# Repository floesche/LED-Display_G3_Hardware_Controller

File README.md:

---
title: Controller PCB
parent: Generation 3
---

# panels_controller_design  

CAD design files, gerber files and parts list for the Panels Controller.

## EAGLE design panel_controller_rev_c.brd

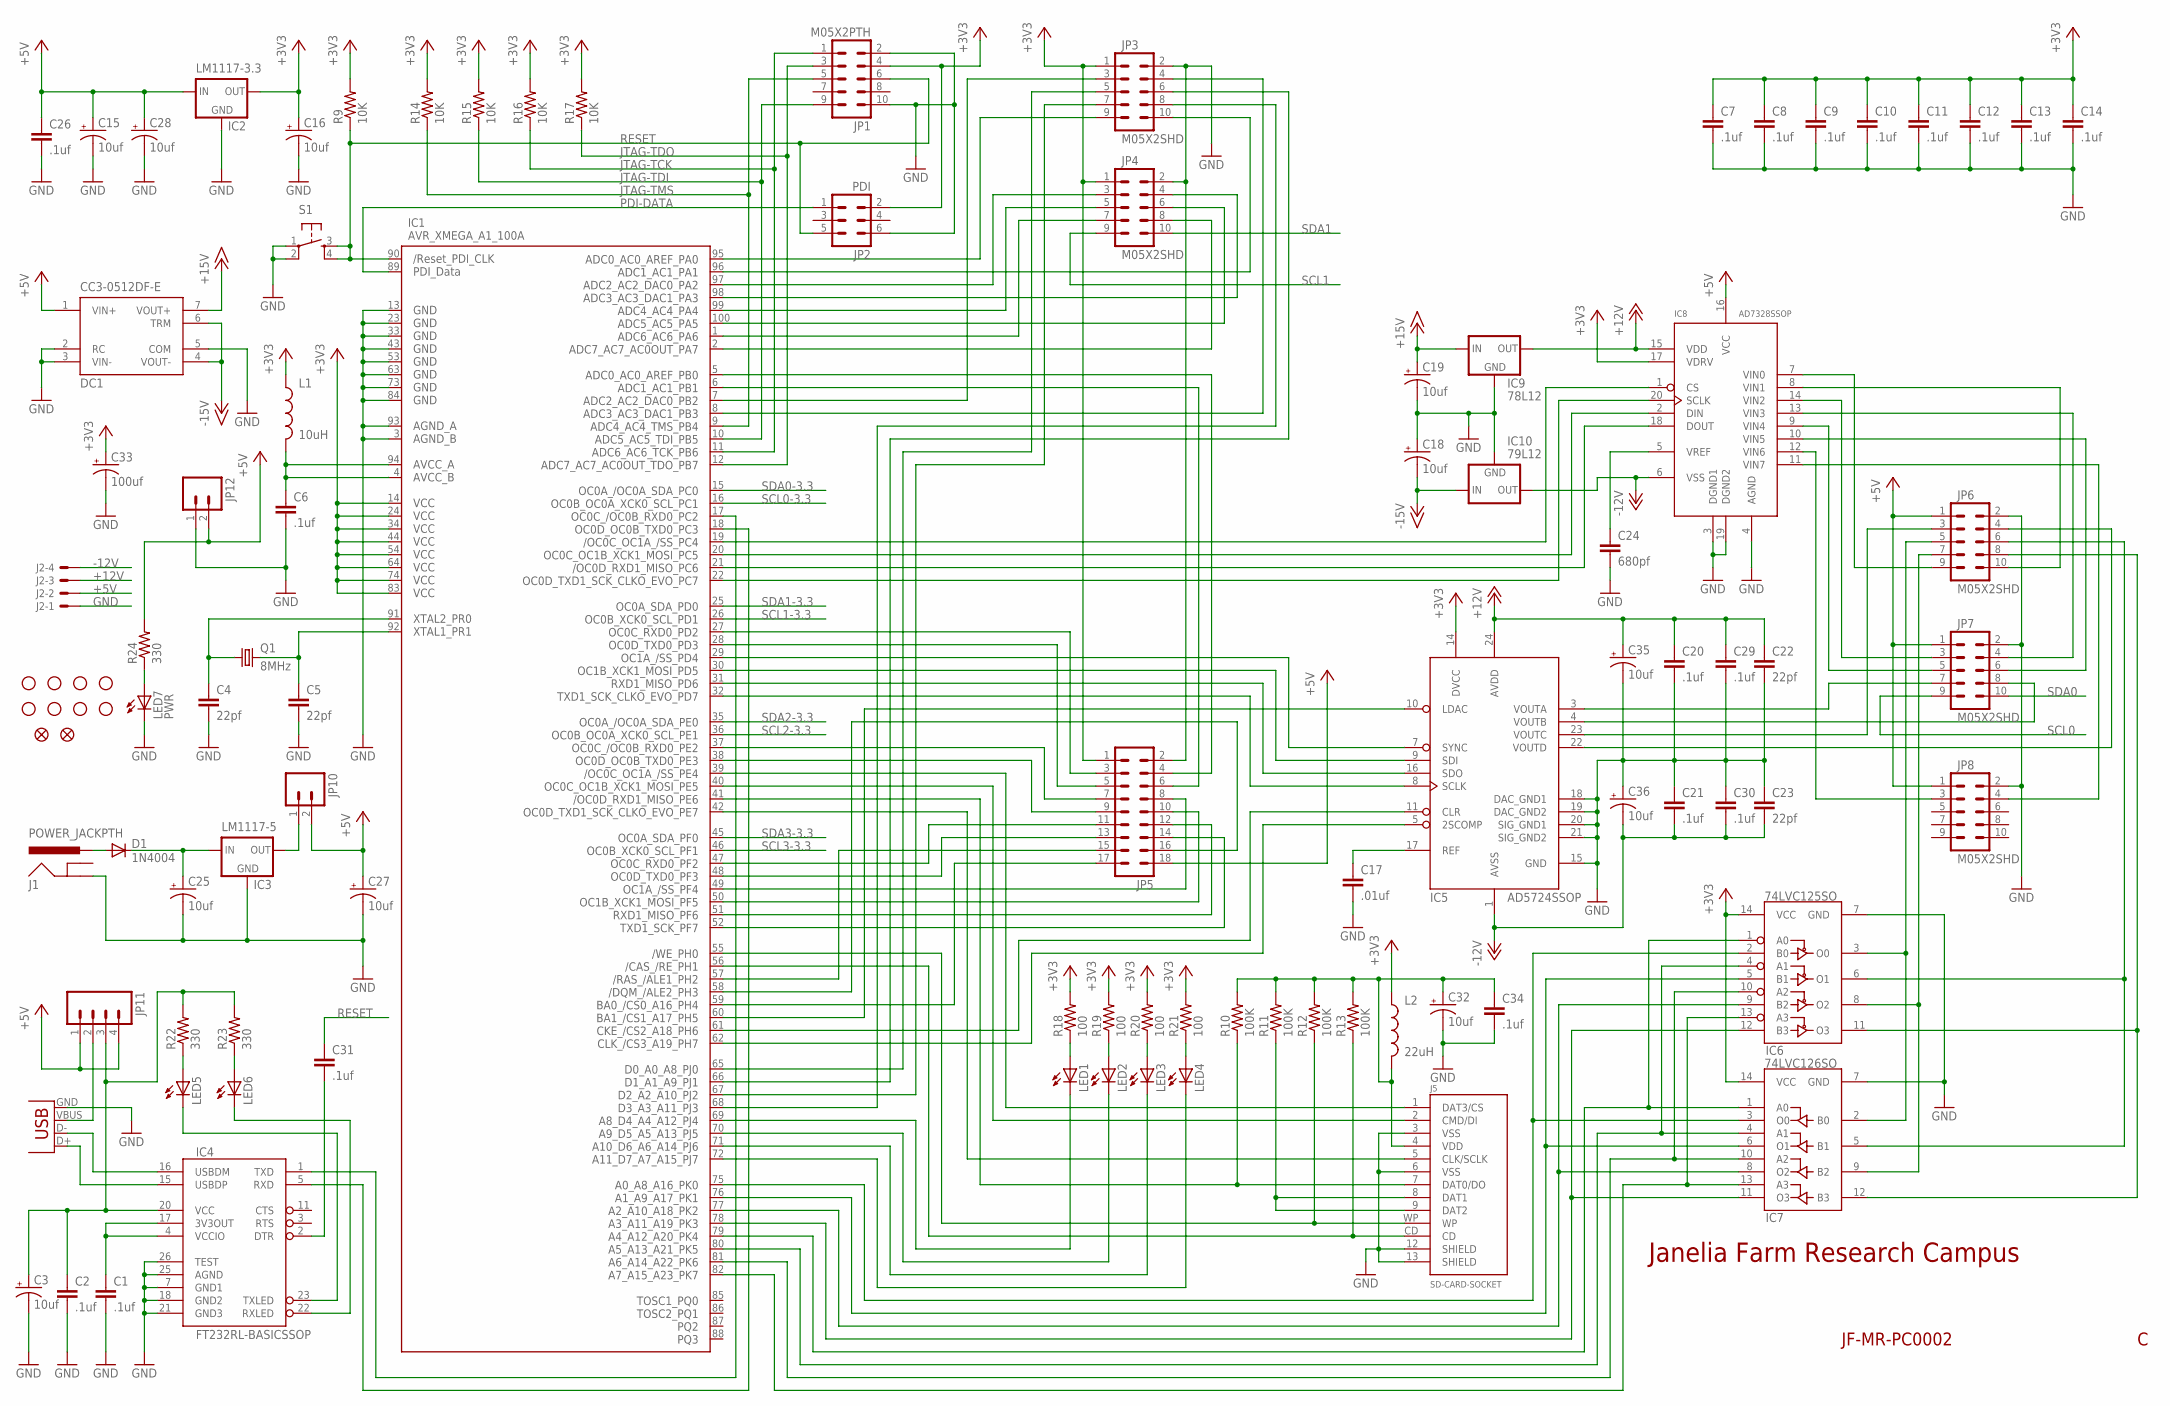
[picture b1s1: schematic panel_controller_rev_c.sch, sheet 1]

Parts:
C1, C2, C6, C7, C8, C9, C10, C11, C12, C13, C14, C20, C21, C26, C29, C30, C31, C34: .1uf; 0603
C3, C15, C16, C18, C19, C25, C27, C28, C32, C35, C36: 10uf; EIA3216
C4, C5, C22, C23: 22pf; 0603
C17: .01uf; 0603
C24: 680pf; 0603
C33: 100uf; PANASONIC_E
D1: 1N4004; DO41-10
DC1: CC3-0512DF-E; CC3-TH
IC1: AVR_XMEGA_A1_100A; TQFP100
IC2: LM1117-3.3; SOT223
IC3: LM1117-5; SOT223
IC4: FT232RL-BASICSSOP; SSOP28DB
IC5: AD5724SSOP; TSSOP24
IC6: 74LVC125SO; SO014
IC7: 74LVC126SO; SO014
IC8: AD7328SSOP; TSSOP20
IC9: 78L12; SOT89
IC10: 79L12; SOT89
J1: POWER_JACKPTH; POWER_JACK_PTH
J2: KK-156-4
J3: USBPTH; USB-B-PTH
J5: SD-CARD-SOCKET; SD-MMC_SOCKET-3M
JP1: M05X2PTH; MA05-2
JP2: PDI; MA03-2
JP3, JP4, JP6, JP7, JP8: M05X2SHD; 2X5-SHROUDED
JP5: MA09-2
JP10, JP12: M02PTH; 1X02
JP11: M04PTH; 1X04
L1: 10uH; 0805
L2: 22uH; 0805
LED1, LED2, LED3, LED4, LED5, LED6: LED3MM
LED7: PWR; LED3MM
Q1: 8MHz; HC49UP
R9, R14, R15, R16, R17: 10K; 0603
R10, R11, R12, R13: 100K; 0603
R18, R19, R20, R21: 100; 0603
R22, R23, R24: 330; 0603
S1: TAC_SWITCHB3S-1000; OMRON
U$1, U$2: FIDUCIAL1X2; FIDUCIAL-1X2
U$3, U$4, U$5, U$6, U$7, U$8, U$9, U$10: STAND-OFF

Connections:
+3V3: C7.1, C8.1, C9.1, C10.1, C11.1, C12.1, C13.1, C14.1, C16.A (+), C33.+, IC1.14 (VCC1), IC1.24 (VCC2), IC1.34 (VCC3), IC1.44 (VCC4), IC1.54 (VCC5), IC1.64 (VCC6), IC1.74 (VCC7), IC1.83 (VCC8), IC2.2 (OUT), IC5.14 (DVCC), IC6.14 (VCC), IC7.14 (VCC), IC8.17 (VDRV), JP1.4, JP2.2, JP3.1, JP4.1, JP5.1, L1.1, L2.1, R9.2, R14.2, R15.2, R16.2, R17.2, R18.2, R19.2, R20.2, R21.2; also elsewhere on the board
+5V: C15.A (+), C26.1, C27.A (+), C28.A (+), DC1.1 (VIN+), IC2.3 (IN), IC8.16 (VCC), J2.2, JP5.18, JP6.1, JP7.1, JP8.1, JP10.2, JP11.1, JP11.4, JP12.2, R24.2; also elsewhere on the board
+12V: C20.1, C22.1, C29.1, C35.A (+), IC5.24 (AVDD), IC8.15 (VDD), IC9.1 (OUT), J2.3
+15V: C19.A (+), DC1.7 (VOUT+), IC9.3 (IN)
-12V: C21.2, C23.2, C30.2, C36.C (-), IC5.1 (AVSS), IC8.6 (VSS), IC10.3 (OUT), J2.4
-15V: C18.C (-), DC1.4 (VOUT-), DC1.6 (TRM), IC10.2 (IN)
GND: C1.2, C2.2, C3.C (-), C4.2, C5.2, C6.2, C7.2, C8.2, C9.2, C10.2, C11.2, C12.2, C13.2, C14.2, C15.C (-), C16.C (-), C17.2, C18.A (+), C19.C (-), C20.2, C21.1, C22.2, C23.1, C24.2, C25.C (-), C26.2, C27.C (-), C28.C (-), C29.2, C30.1, C32.C (-), C33.-, C34.2, C35.C (-), C36.A (+), DC1.2 (RC), DC1.3 (VIN-), DC1.5 (COM), IC1.3 (AGND_B), IC1.13 (GND1), IC1.23 (GND2), IC1.33 (GND3), IC1.43 (GND4), IC1.53 (GND5), IC1.63 (GND6), IC1.73 (GND7), IC1.84 (GND8), IC1.93 (AGND_A), IC2.1 (GND), IC3.1 (GND), IC4.7 (GND1), IC4.18 (GND2), IC4.21 (GND3), IC4.25 (AGND), IC4.26 (TEST), IC5.15 (GND), IC5.18 (DAC_GND1), IC5.19 (DAC_GND2), IC5.20 (SIG_GND1), IC5.21 (SIG_GND2), IC6.7 (GND), IC7.7 (GND), IC8.3 (DGND1), IC8.4 (AGND), IC8.19 (DGND2), IC9.2 (GND), IC10.1 (GND), J1.GND, J2.1, J3.GND, J5.3 (VSS), J5.6 (VSS), J5.12 (SHIELD), J5.13 (SHIELD), JP1.2, JP1.10, JP2.6, JP3.2, JP4.2, JP5.2, JP6.2, JP7.2, JP8.2, JP12.1, LED7.K (C), S1.1, S1.2; also elsewhere on the board
JTAG-TCK: IC1.11 (PB6), JP1.1, R16.1
JTAG-TDI: IC1.10 (PB5), JP1.9, R15.1
JTAG-TDO: IC1.12 (PB7), JP1.3, R17.1
JTAG-TMS: IC1.9 (PB4), JP1.5, R14.1
unnamed: IC4.16 (USBDM), J3.D-
unnamed: IC4.15 (USBDP), J3.D+
unnamed: J3.VBUS, JP11.2
unnamed: C1.1, IC4.4 (VCCIO), IC4.17 (3V3OUT)
unnamed: IC1.18 (PC3), IC4.5 (RXD)
unnamed: IC1.19 (PC4), IC8.1 (CS)
unnamed: IC1.57 (PH2), JP5.15
unnamed: IC1.65 (PJ0), JP3.5
unnamed: IC1.67 (PJ2), JP3.7
unnamed: IC1.17 (PC2), IC4.1 (TXD)
unnamed: LED5.A, R22.1
unnamed: IC1.40 (PE5), J5.2 (CMD/DI)
unnamed: IC1.41 (PE6), J5.7 (DAT0/DO), R10.1
unnamed: IC1.42 (PE7), J5.5 (CLK/SCLK)
unnamed: IC1.39 (PE4), J5.1 (DAT3/CS)
unnamed: IC1.69 (PJ4), LED1.K (C)
unnamed: IC1.70 (PJ5), LED2.K (C)
unnamed: C4.1, IC1.91 (PR0), Q1.1
unnamed: C5.1, IC1.92 (PR1), Q1.2
unnamed: IC1.71 (PJ6), LED3.K (C)
unnamed: IC1.72 (PJ7), LED4.K (C)
unnamed: LED1.A, R18.1
unnamed: C6.1, IC1.4 (AVCC_B), IC1.94 (AVCC_A), L1.2
unnamed: LED2.A, R19.1
unnamed: LED3.A, R20.1
unnamed: LED4.A, R21.1
unnamed: IC1.66 (PJ1), JP3.6
unnamed: IC1.68 (PJ3), JP3.8
unnamed: IC1.2 (PA7), JP4.8
unnamed: IC1.1 (PA6), JP4.7
unnamed: IC1.100 (PA5), JP4.6
unnamed: J5.8 (DAT1), J5.9 (DAT2), R11.1
unnamed: IC1.55 (PH0), J5.WP, R12.1
unnamed: IC1.56 (PH1), J5.CD, R13.1
unnamed: IC1.99 (PA4), JP4.5
unnamed: IC1.98 (PA3), JP4.4
unnamed: IC1.97 (PA2), JP4.3
unnamed: IC1.96 (PA1), JP3.10
unnamed: IC1.95 (PA0), JP3.9
unnamed: IC1.7 (PB2), JP3.3
unnamed: IC1.8 (PB3), JP3.4
unnamed: IC1.20 (PC5), IC8.2 (DIN)
unnamed: IC1.22 (PC7), IC8.20 (SCLK)
unnamed: IC1.21 (PC6), IC8.18 (DOUT)
unnamed: IC1.32 (PD7), IC5.8 (SCLK)
unnamed: LED6.A, R23.1
unnamed: C24.1, IC8.5 (VREF)
unnamed: IC1.31 (PD6), IC5.16 (SDO)
unnamed: IC1.30 (PD5), IC5.9 (SDI)
unnamed: IC1.29 (PD4), IC5.7 (SYNC)
unnamed: IC1.61 (PH6), IC5.11 (CLR)
unnamed: C17.1, IC5.17 (REF)
unnamed: IC1.37 (PE2), JP5.7
unnamed: IC1.38 (PE3), JP5.9
unnamed: IC1.27 (PD2), JP5.3
unnamed: IC1.28 (PD3), JP5.5
unnamed: IC1.5 (PB0), JP5.4
unnamed: IC1.6 (PB1), JP5.6
unnamed: IC1.47 (PF2), JP5.11
unnamed: IC1.48 (PF3), JP5.13
unnamed: IC1.49 (PF4), JP5.8
unnamed: IC1.50 (PF5), JP5.10
unnamed: IC1.51 (PF6), JP5.12
unnamed: IC1.52 (PF7), JP5.14
unnamed: IC1.62 (PH7), IC5.5 (2SCOMP)
unnamed: IC1.75 (PK0), IC6.2 (B0), IC7.3 (O0)
unnamed: IC1.76 (PK1), IC6.5 (B1), IC7.6 (O1)
unnamed: IC1.77 (PK2), IC6.9 (B2), IC7.8 (O2)
unnamed: IC1.78 (PK3), IC6.12 (B3), IC7.11 (O3)
unnamed: IC1.79 (PK4), IC6.1 (A0), IC7.1 (A0)
unnamed: C2.1, C3.A (+), IC4.20 (VCC), JP11.3, R22.2, R23.2
unnamed: IC4.22 (RXLED), LED6.K (C)
unnamed: IC1.60 (PH5), IC5.10 (LDAC)
unnamed: IC8.11 (VIN7), JP8.4
unnamed: IC8.7 (VIN0), JP6.9
unnamed: IC8.8 (VIN1), JP6.10
unnamed: IC8.14 (VIN2), JP7.3
unnamed: IC8.13 (VIN3), JP7.4
unnamed: IC8.9 (VIN4), JP7.5
unnamed: IC8.10 (VIN5), JP7.6
unnamed: IC5.23 (VOUTC), JP6.3
unnamed: IC8.12 (VIN6), JP8.3
unnamed: IC5.3 (VOUTA), JP7.7
unnamed: IC5.4 (VOUTB), JP7.8
unnamed: IC5.22 (VOUTD), JP6.4
unnamed: C32.A (+), C34.1, J5.4 (VDD), L2.2, R10.2, R11.2, R12.2, R13.2
unnamed: IC1.80 (PK5), IC6.4 (A1), IC7.4 (A1)
unnamed: IC1.81 (PK6), IC6.10 (A2), IC7.10 (A2)
unnamed: IC1.82 (PK7), IC6.13 (A3), IC7.13 (A3)
unnamed: IC4.23 (TXLED), LED5.K (C)
unnamed: IC6.3 (O0), IC7.2 (B0), JP6.5
unnamed: IC6.6 (O1), IC7.5 (B1), JP6.6
unnamed: IC6.8 (O2), IC7.9 (B2), JP6.7
unnamed: IC6.11 (O3), IC7.12 (B3), JP6.8
unnamed: IC1.59 (PH4), JP5.17
unnamed: IC1.58 (PH3), JP5.16
unnamed: LED7.A, R24.1
unnamed: C31.2, IC4.2 (DTR)
unnamed: D1.A, J1.PWR
unnamed: C25.A (+), D1.C, IC3.3 (IN)
unnamed: IC3.2 (OUT), JP10.1
PDI-DATA: IC1.89 (PDI_DATA), JP2.1
RESET: C31.1, IC1.90 (RESET), JP1.6, JP2.5, R9.1, S1.3, S1.4
SCL0: JP7.9; also elsewhere on the board
SCL0-3.3: IC1.16 (PC1); also elsewhere on the board
SCL1: JP4.9; also elsewhere on the board
SCL1-3.3: IC1.26 (PD1); also elsewhere on the board
SCL2-3.3: IC1.36 (PE1); also elsewhere on the board
SCL3-3.3: IC1.46 (PF1); also elsewhere on the board
SDA0: JP7.10; also elsewhere on the board
SDA0-3.3: IC1.15 (PC0); also elsewhere on the board
SDA1: JP4.10; also elsewhere on the board
SDA1-3.3: IC1.25 (PD0); also elsewhere on the board
SDA2-3.3: IC1.35 (PE0); also elsewhere on the board
SDA3-3.3: IC1.45 (PF0); also elsewhere on the board

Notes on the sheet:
Janelia Farm Research Campus
JF-MR-PC0002

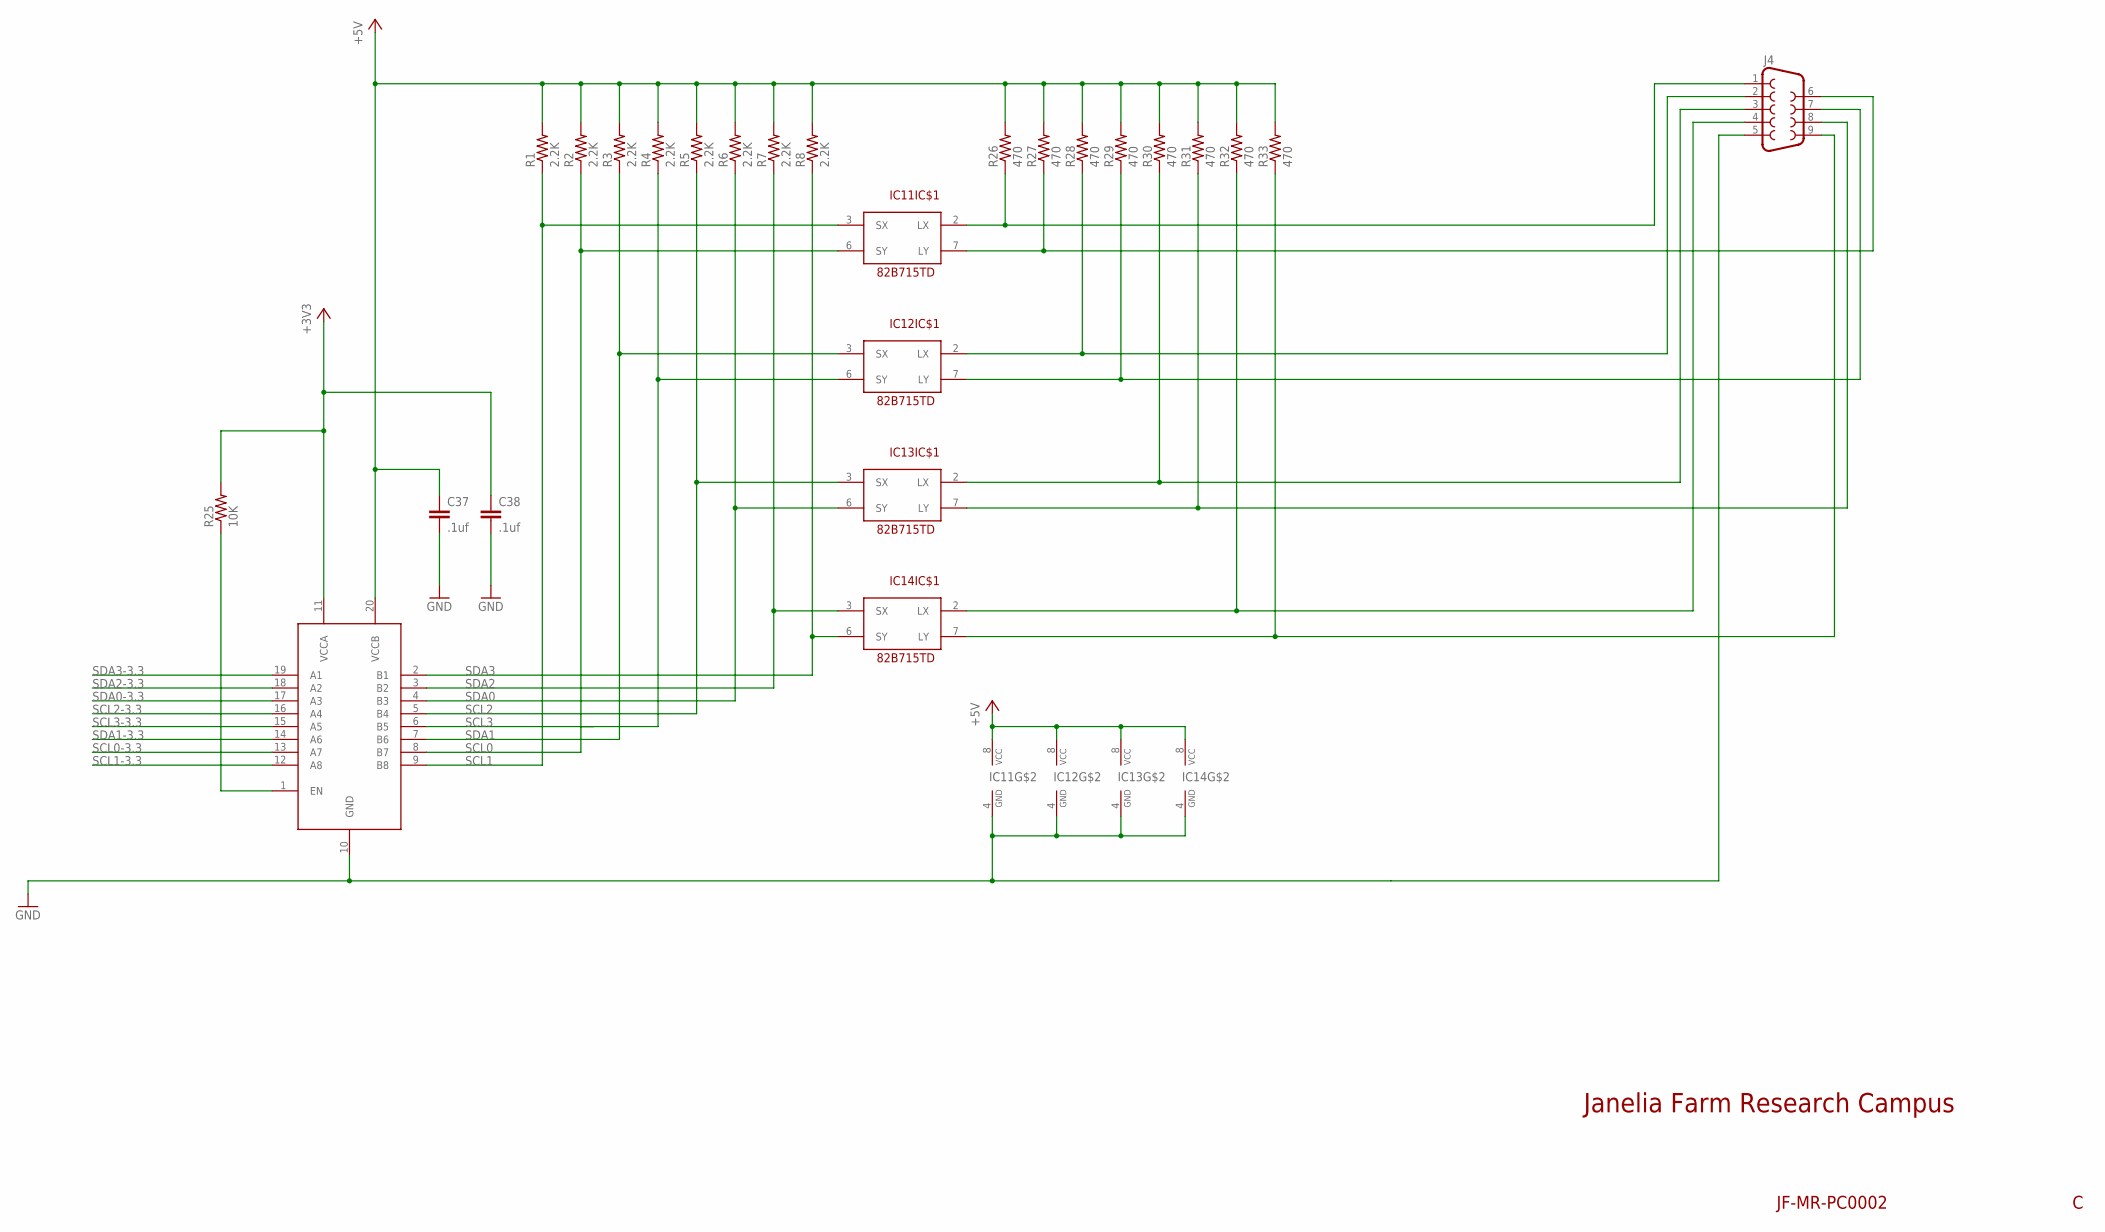
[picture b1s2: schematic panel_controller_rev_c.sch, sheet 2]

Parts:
C37, C38: .1uf; 0603
IC11, IC12, IC13, IC14: 82B715TD; SO08
IC15: PCA9519; TSSOP20
J4: DB9
R1, R2, R3, R4, R5, R6, R7, R8: 2.2K; 0603
R25: 10K; 0603
R26, R27, R28, R29, R30, R31, R32, R33: 470; 0603

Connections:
+3V3: C38.1, IC15.11 (VCCA), R25.2; also elsewhere on the board
+5V: C37.1, IC11.8 (VCC), IC12.8 (VCC), IC13.8 (VCC), IC14.8 (VCC), IC15.20 (VCCB), R1.2, R2.2, R3.2, R4.2, R5.2, R6.2, R7.2, R8.2, R26.2, R27.2, R28.2, R29.2, R30.2, R31.2, R32.2, R33.2; also elsewhere on the board
GND: C37.2, C38.2, IC11.4 (GND), IC12.4 (GND), IC13.4 (GND), IC14.4 (GND), IC15.10 (GND), J4.5; also elsewhere on the board
unnamed: IC12.2 (LX), J4.2, R28.1
unnamed: IC12.7 (LY), J4.7, R29.1
unnamed: IC13.2 (LX), J4.3, R30.1
unnamed: IC14.2 (LX), J4.4, R32.1
unnamed: IC14.7 (LY), J4.9, R33.1
unnamed: IC13.7 (LY), J4.8, R31.1
unnamed: IC11.7 (LY), J4.6, R27.1
unnamed: IC11.2 (LX), J4.1, R26.1
unnamed: IC15.1 (EN), R25.1
SCL0: IC11.6 (SY), IC15.8 (B7), R2.1; also elsewhere on the board
SCL0-3.3: IC15.13 (A7); also elsewhere on the board
SCL1: IC11.3 (SX), IC15.9 (B8), R1.1; also elsewhere on the board
SCL1-3.3: IC15.12 (A8); also elsewhere on the board
SCL2: IC13.3 (SX), IC15.5 (B4), R5.1
SCL2-3.3: IC15.16 (A4); also elsewhere on the board
SCL3: IC12.6 (SY), IC15.6 (B5), R4.1
SCL3-3.3: IC15.15 (A5); also elsewhere on the board
SDA0: IC13.6 (SY), IC15.4 (B3), R6.1; also elsewhere on the board
SDA0-3.3: IC15.17 (A3); also elsewhere on the board
SDA1: IC12.3 (SX), IC15.7 (B6), R3.1; also elsewhere on the board
SDA1-3.3: IC15.14 (A6); also elsewhere on the board
SDA2: IC14.3 (SX), IC15.3 (B2), R7.1
SDA2-3.3: IC15.18 (A2); also elsewhere on the board
SDA3: IC14.6 (SY), IC15.2 (B1), R8.1
SDA3-3.3: IC15.19 (A1); also elsewhere on the board

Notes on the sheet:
Janelia Farm Research Campus
JF-MR-PC0002

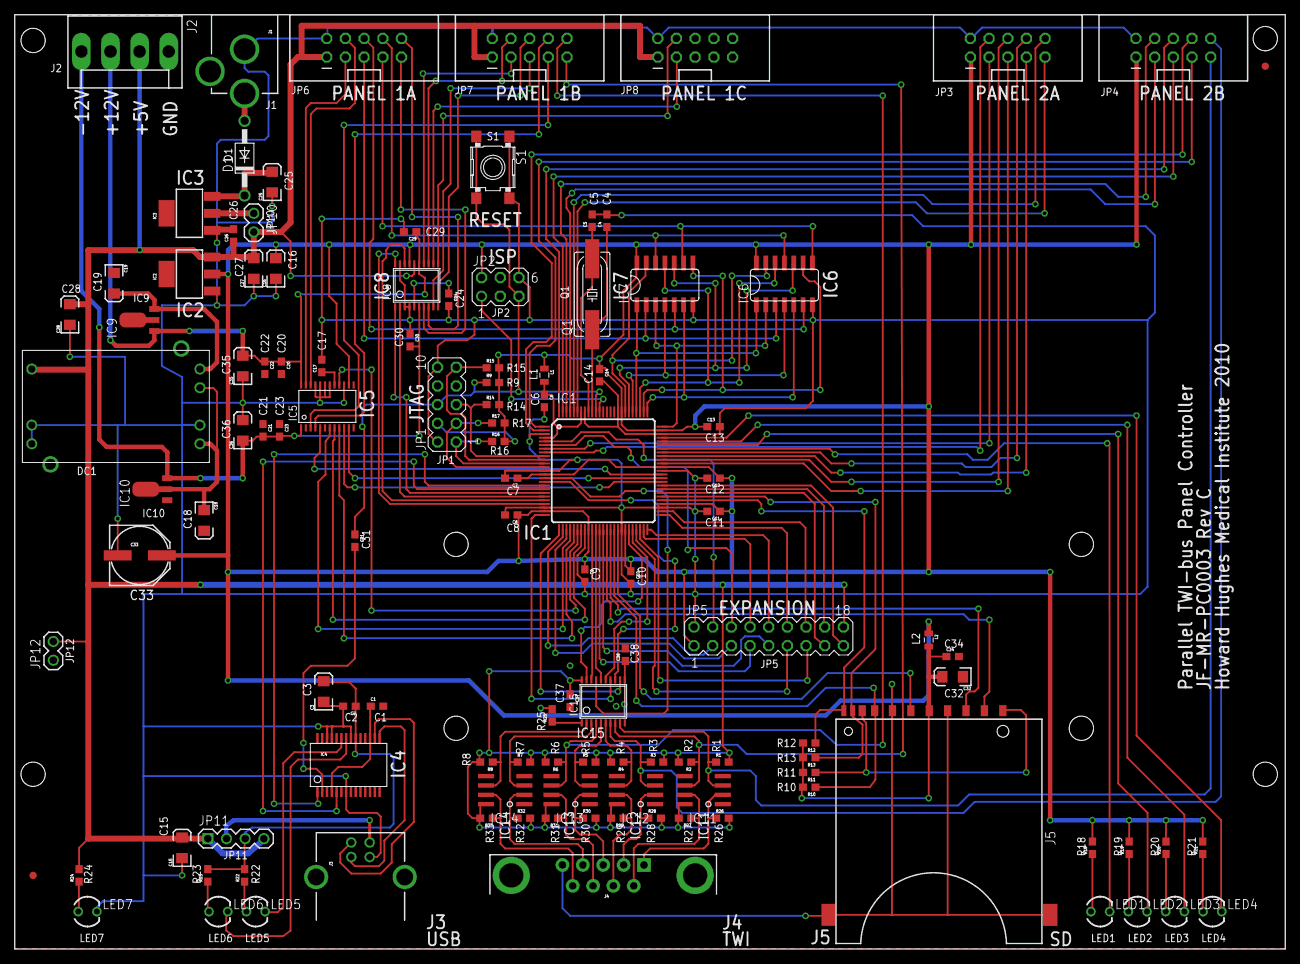
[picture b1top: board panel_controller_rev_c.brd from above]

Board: 2 copper layers, 172.7 x 127.0 mm, 125 parts (0 on the bottom side), 139 nets.

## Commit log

2018-11-13 Project creation.
2020-08-06 getting ready for panel page
2021-07-08 add schematic as PDF
2021-07-10 add order reference
2021-07-15 typo
2021-11-09 fix assets
2021-11-10 add links to ISP and BNC
2021-11-10 consistent file naming
2021-11-12 clean up controller
2021-11-19 optimize images
2022-11-08 fix link
